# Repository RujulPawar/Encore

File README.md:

## **Buck Converter Design and Simulation**

### **Team Information**
- **Team Leader**:
  - Rujul Pawar
- **Team Members**: 
  - Samar Mhetre

### **Project Overview**
This repository is for the **Encore Pre-qualifier Challenge 2024-25**, focusing on designing a **buck converter**. The main objectives of this project are:
- **Input Voltage**: 24V DC (1A max)
- **Output Voltage**: 5V DC
- **Target Efficiency**: 90% or higher

### **Repository Structure**
- **Datasheets/**: Relevant component datasheets.
- **KicadFiles/**: Schematic and PCB layout files created using **KiCad**.
- **BuckConverterLtspice.asc**: LTSpice simulation file for testing the design.
- **EncoreBom.csv**: Bill of Materials (BoM) detailing components used.

### **Simulation and PCB Design**
- **Simulation**: To verify the circuit, open and run `BuckConverterLtspice.asc` in **LTSpice**.
- **PCB Layout**: A dual-layer PCB design with a maximum size of **10cm x 5cm**, created using **KiCad**.

### **References**
- [Texas Instruments SLVA477B Design Guide](https://www.ti.com/lit/an/slva477b/slva477b.pdf)

---

This document serves as a concise guide to the contents and structure of this repository. For further details, explore the files and links provided.

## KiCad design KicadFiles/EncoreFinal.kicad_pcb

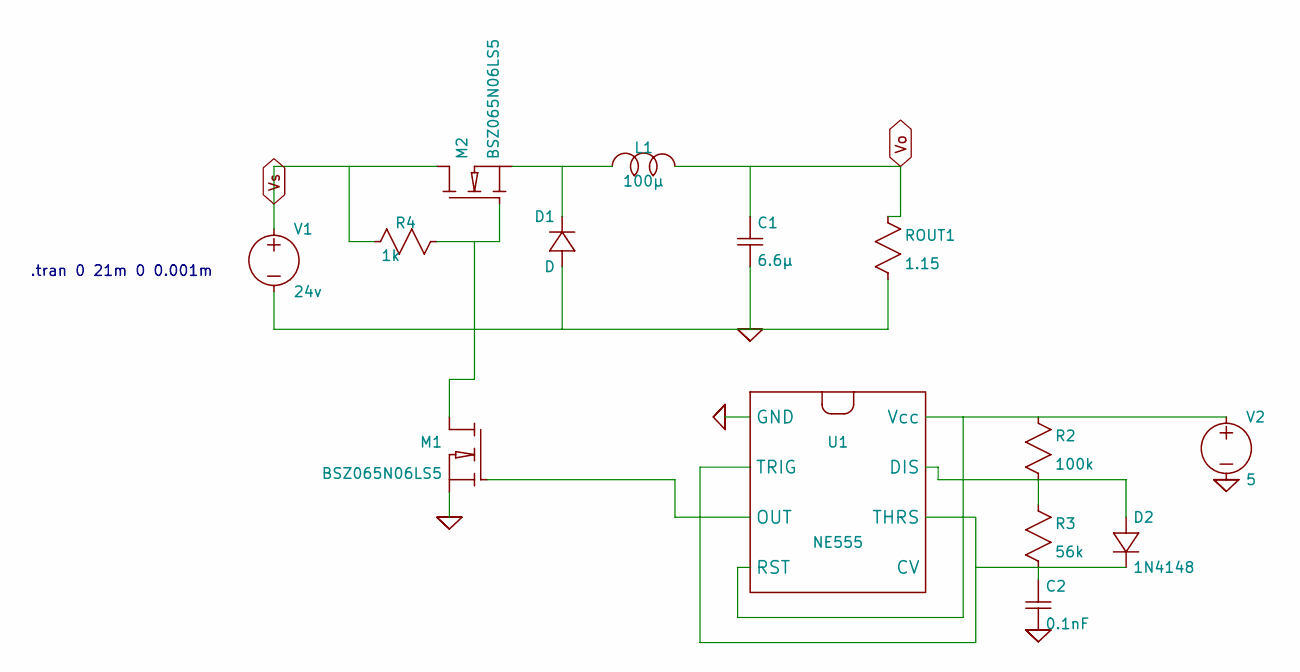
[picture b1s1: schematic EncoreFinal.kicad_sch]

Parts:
C1: 6.6µ; CP_Elec_3x5.3
C2: 0.1nF; CP_Elec_3x5.3
D1: D; D_0201_0603Metric
D2: 1N4148; D_0201_0603Metric
L1: 100µ; L_Axial_L5.0mm_D3.6mm_P10.00mm_Horizontal_Murata_BL01RN1A2A2
M1, M2: BSZ065N06LS5; DirectFET_L4
R2: 100k; R_0201_0603Metric
R3: 56k; R_0201_0603Metric
R4: 1k; R_0201_0603Metric
ROUT1: 1.15; R_0201_0603Metric
U1: NE555; SOIC-8_3.9x4.9mm_P1.27mm
V1: 24v; TerminalBlock_MetzConnect_Type011_RT05502HBWC_1x02_P5.00mm_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
V2: 5; TerminalBlock_MetzConnect_Type011_RT05502HBWC_1x02_P5.00mm_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

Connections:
0: C1.2, C2.2, D1.1 (+), M1.3 (S), ROUT1.2, U1.1 (GND), V1.2 (-), V2.2 (-)
unnamed: D1.2 (-), L1.1, M2.3 (S)
unnamed: D2.1 (+), R2.2, R3.1, U1.7 (DIS)
unnamed: C2.1, D2.2 (-), R3.2, U1.2 (TRIG), U1.6 (THRS)
unnamed: M1.1 (D), M2.2 (G), R4.1
unnamed: M1.2 (G), U1.3 (OUT)
unnamed: R2.1, U1.4 (RST), U1.8 (Vcc), V2.1 (+)
Vo: C1.1, L1.2, ROUT1.1
Vs: M2.1 (D), R4.2, V1.1 (+)

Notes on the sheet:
.tran 0 21m 0 0.001m

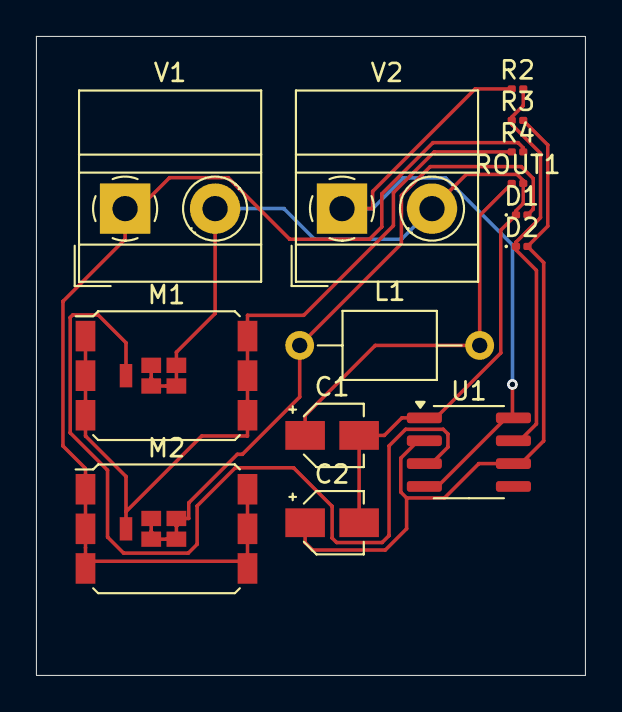
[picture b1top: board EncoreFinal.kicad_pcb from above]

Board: 2 copper layers, 30.5 x 35.5 mm, 14 parts (0 on the bottom side), 9 nets.

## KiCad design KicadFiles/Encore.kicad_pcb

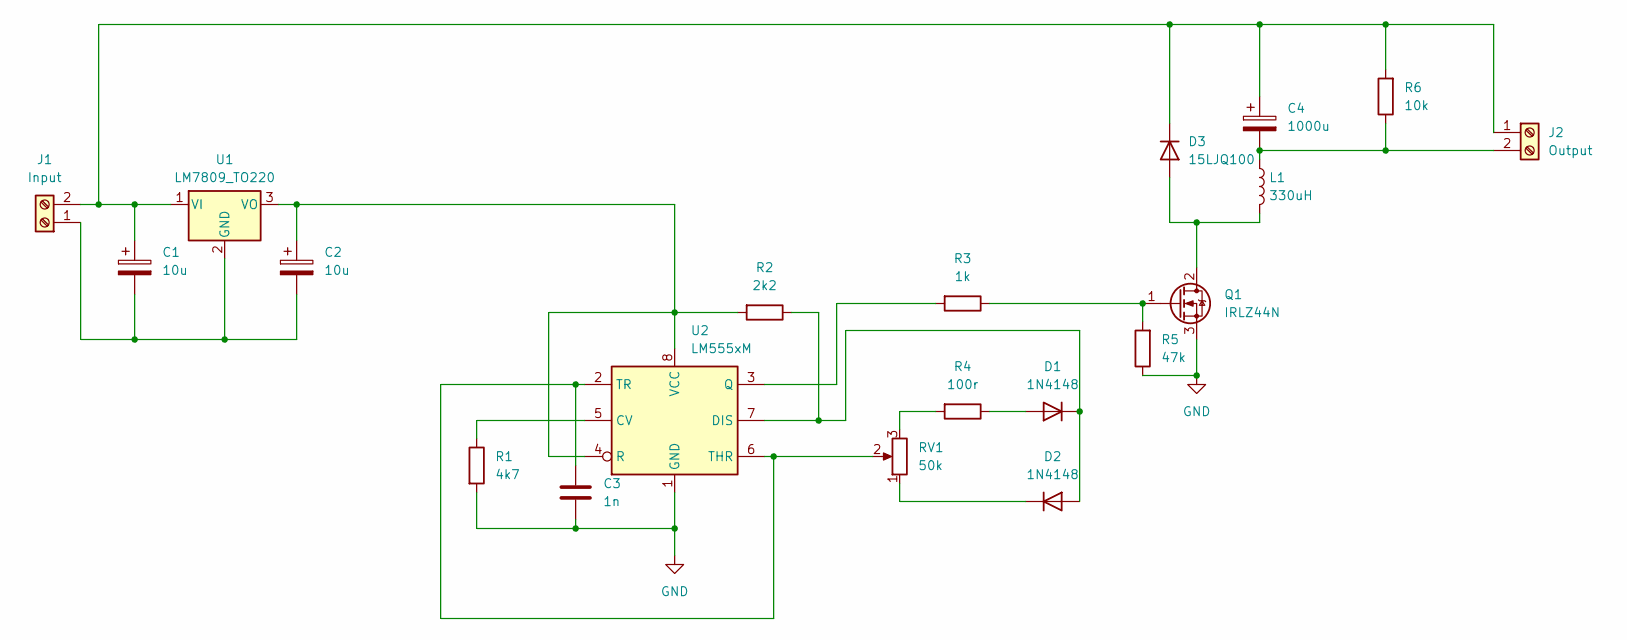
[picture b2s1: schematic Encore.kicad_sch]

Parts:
C1, C2: 10u; CP_Elec_3x5.3
C3: 1n; CP_Elec_3x5.3
C4: 1000u; CP_Elec_3x5.3
D1, D2: 1N4148; D_0201_0603Metric
D3: 15LJQ100; D_0201_0603Metric
J1: Input; TerminalBlock_MetzConnect_Type011_RT05502HBWC_1x02_P5.00mm_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
J2: Output; TerminalBlock_MetzConnect_Type011_RT05502HBWC_1x02_P5.00mm_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
L1: 330uH; L_0201_0603Metric
Q1: IRLZ44N; TO-220-3_Vertical
R1: 4k7; R_0201_0603Metric
R2: 2k2; R_0201_0603Metric
R3: 1k; R_0201_0603Metric
R4: 100r; R_0201_0603Metric
R5: 47k; R_0201_0603Metric
R6: 10k; R_0201_0603Metric
RV1: 50k; Potentiometer_ACP_CA6-VSMD_Vertical
U1: LM7809_TO220; TO-220-3_Vertical
U2: LM555xM; SOIC-8_3.9x4.9mm_P1.27mm

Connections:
GND: C3.2, Q1.3 (S), R1.2, R5.1, U2.1 (GND)
unnamed: D1.2 (A), R4.1
unnamed: D1.1 (K), D2.2 (A), R2.1, U2.7 (DIS)
unnamed: D2.1 (K), RV1.1
unnamed: D3.2 (A), L1.2, Q1.2 (D)
unnamed: C1.1, C4.1, D3.1 (K), J1.2, J2.1, R6.2, U1.1 (VI)
unnamed: C1.2, C2.2, J1.1, U1.2 (GND)
unnamed: C4.2, J2.2, L1.1, R6.1
unnamed: Q1.1 (G), R3.1, R5.2
unnamed: R4.2, RV1.3
unnamed: C2.1, R2.2, U1.3 (VO), U2.4 (R), U2.8 (VCC)
unnamed: R1.1, U2.5 (CV)
unnamed: R3.2, U2.3 (Q)
unnamed: C3.1, RV1.2, U2.2 (TR), U2.6 (THR)

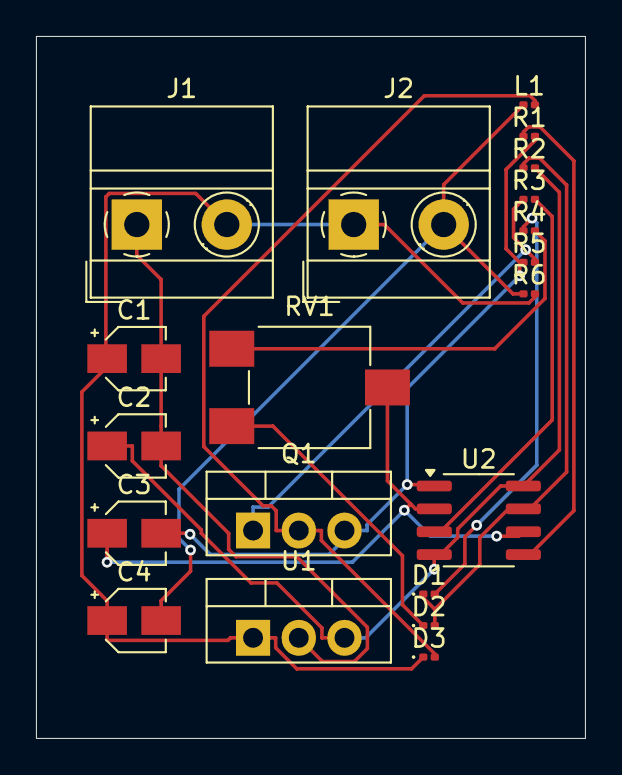
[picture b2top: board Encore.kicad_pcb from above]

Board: 2 copper layers, 30.5 x 39.0 mm, 20 parts (0 on the bottom side), 14 nets.

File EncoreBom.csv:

"Reference","Value","Datasheet","Footprint","Qty","DNP"
"C1,C2","10u","~","Capacitor_SMD:CP_Elec_3x5.3","2",""
"C3","1n","~","Capacitor_SMD:CP_Elec_3x5.3","1",""
"C4","1000u","~","Capacitor_SMD:CP_Elec_3x5.3","1",""
"D1,D2","1N4148","~","Diode_SMD:D_0201_0603Metric","2",""
"D3","15LJQ100","~","Diode_SMD:D_0201_0603Metric","1",""
"J1","Input","~","TerminalBlock_MetzConnect:TerminalBlock_MetzConnect_Type011_RT05502HBWC_1x02_P5.00mm_Horizontal","1",""
"J2","Output","~","TerminalBlock_MetzConnect:TerminalBlock_MetzConnect_Type011_RT05502HBWC_1x02_P5.00mm_Horizontal","1",""
"L1","330uH","~","Inductor_SMD:L_0201_0603Metric","1",""
"Q1","IRLZ44N","http://www.irf.com/product-info/datasheets/data/irlz44n.pdf","Package_TO_SOT_THT:TO-220-3_Vertical","1",""
"R1","4k7","~","Resistor_SMD:R_0201_0603Metric","1",""
"R2","2k2","~","Resistor_SMD:R_0201_0603Metric","1",""
"R3","1k","~","Resistor_SMD:R_0201_0603Metric","1",""
"R4","100r","~","Resistor_SMD:R_0201_0603Metric","1",""
"R5","47k","~","Resistor_SMD:R_0201_0603Metric","1",""
"R6","10k","~","Resistor_SMD:R_0201_0603Metric","1",""
"RV1","50k","~","Potentiometer_SMD:Potentiometer_ACP_CA6-VSMD_Vertical","1",""
"U1","LM7809_TO220","https://www.onsemi.cn/PowerSolutions/document/MC7800-D.PDF","Package_TO_SOT_THT:TO-220-3_Vertical","1",""
"U2","LM555xM","http://www.ti.com/lit/ds/symlink/lm555.pdf","Package_SO:SOIC-8_3.9x4.9mm_P1.27mm","1",""

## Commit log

2024-09-27 Create Datasheets
2024-09-27 Create temp
